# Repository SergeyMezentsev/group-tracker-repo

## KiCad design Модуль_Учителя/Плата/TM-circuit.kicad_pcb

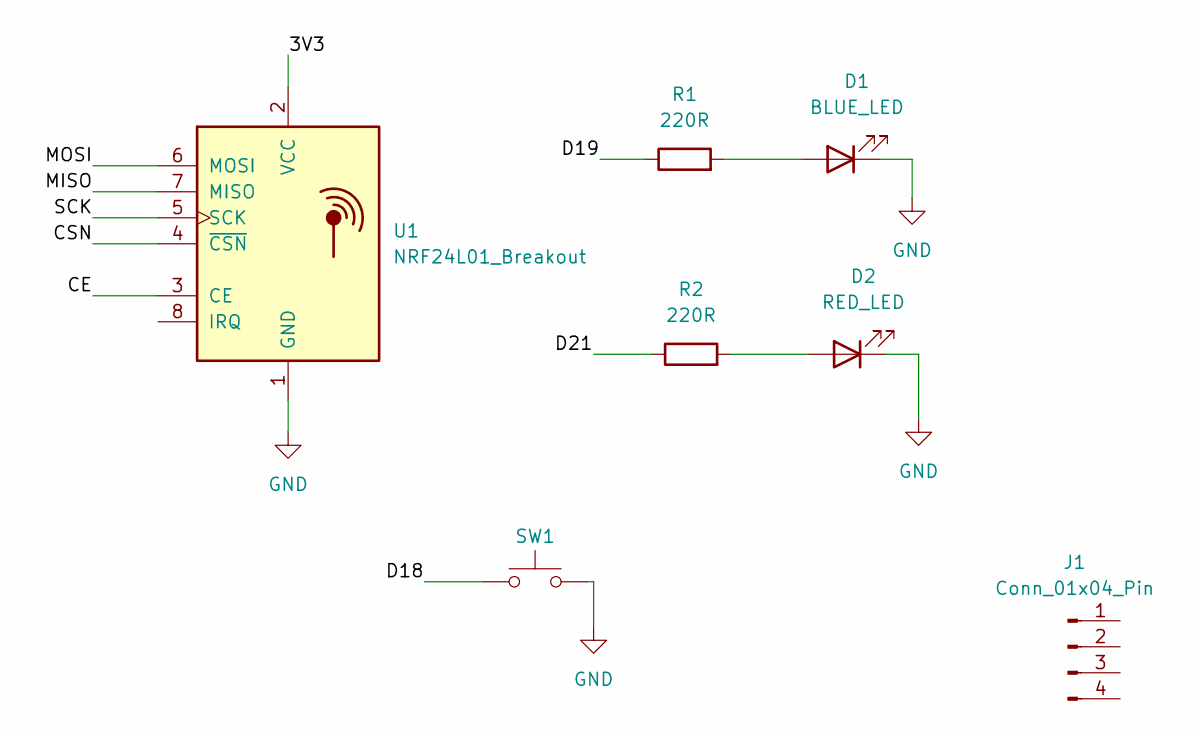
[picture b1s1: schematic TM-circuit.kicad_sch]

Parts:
D1: BLUE_LED; LED_D5.0mm
D2: RED_LED; LED_D5.0mm
J1: Conn_01x04_Pin; PinHeader_1x04_P2.54mm_Vertical
R1, R2: 220R; R_Axial_DIN0207_L6.3mm_D2.5mm_P7.62mm_Horizontal
SW1: SW_Push; SW_PUSH_6mm
U1: NRF24L01_Breakout; nRF24L01_Breakout

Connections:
/3V3: J1.4, U1.2 (VCC)
/CE: U1.3 (CE)
/CSN: U1.4 (~CSN)
/D18: SW1.1
/D19: R1.1
/D21: R2.1
/MISO: U1.7 (MISO)
/MOSI: U1.6 (MOSI)
/SCK: U1.5 (SCK)
GND: D1.1 (K), D2.1 (K), J1.1, SW1.2, U1.1 (GND)
IRQ: U1.8 (IRQ)
unnamed: D1.2 (A), R1.2
unnamed: D2.2 (A), R2.2
RX2: J1.2
TX2: J1.3

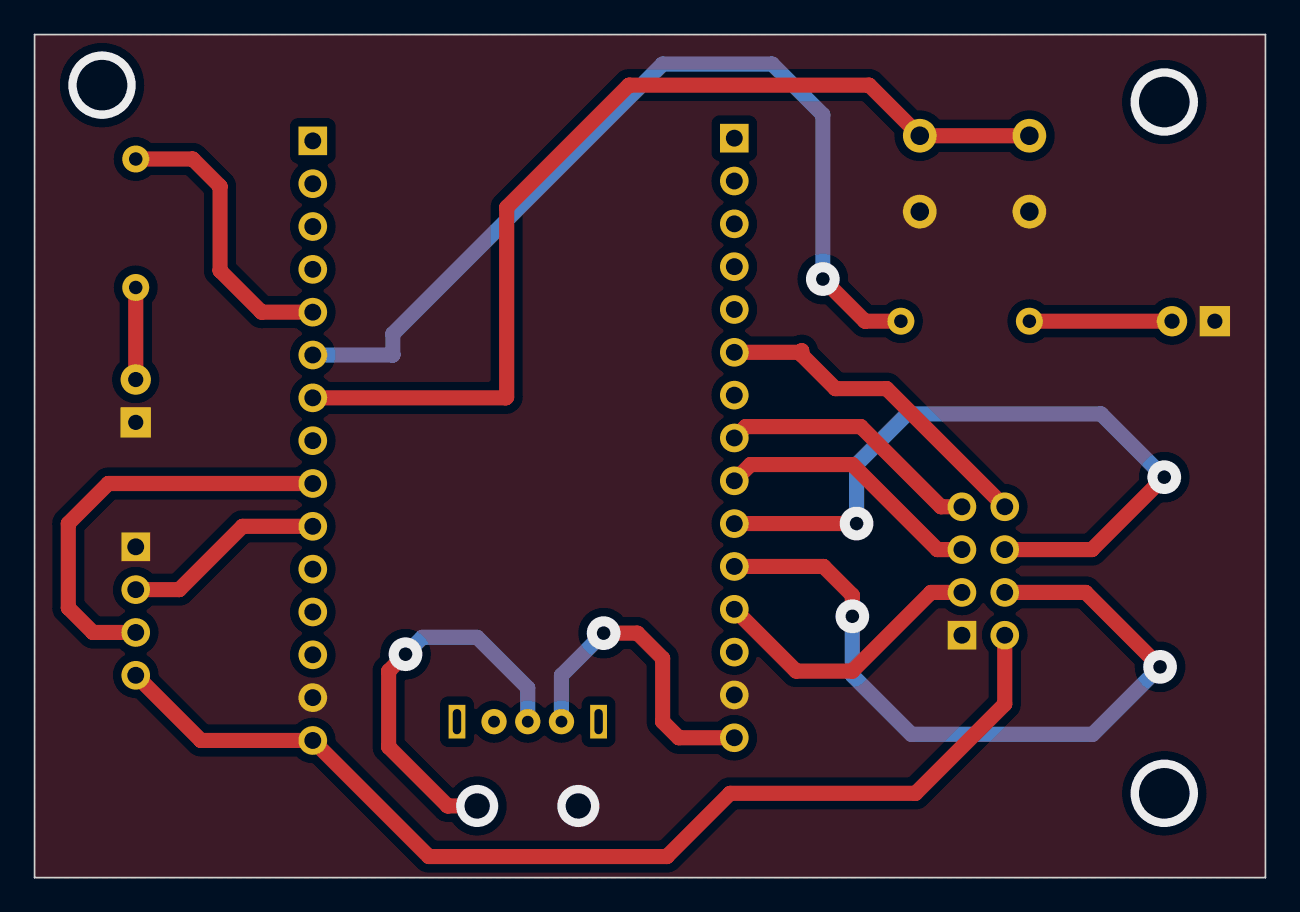
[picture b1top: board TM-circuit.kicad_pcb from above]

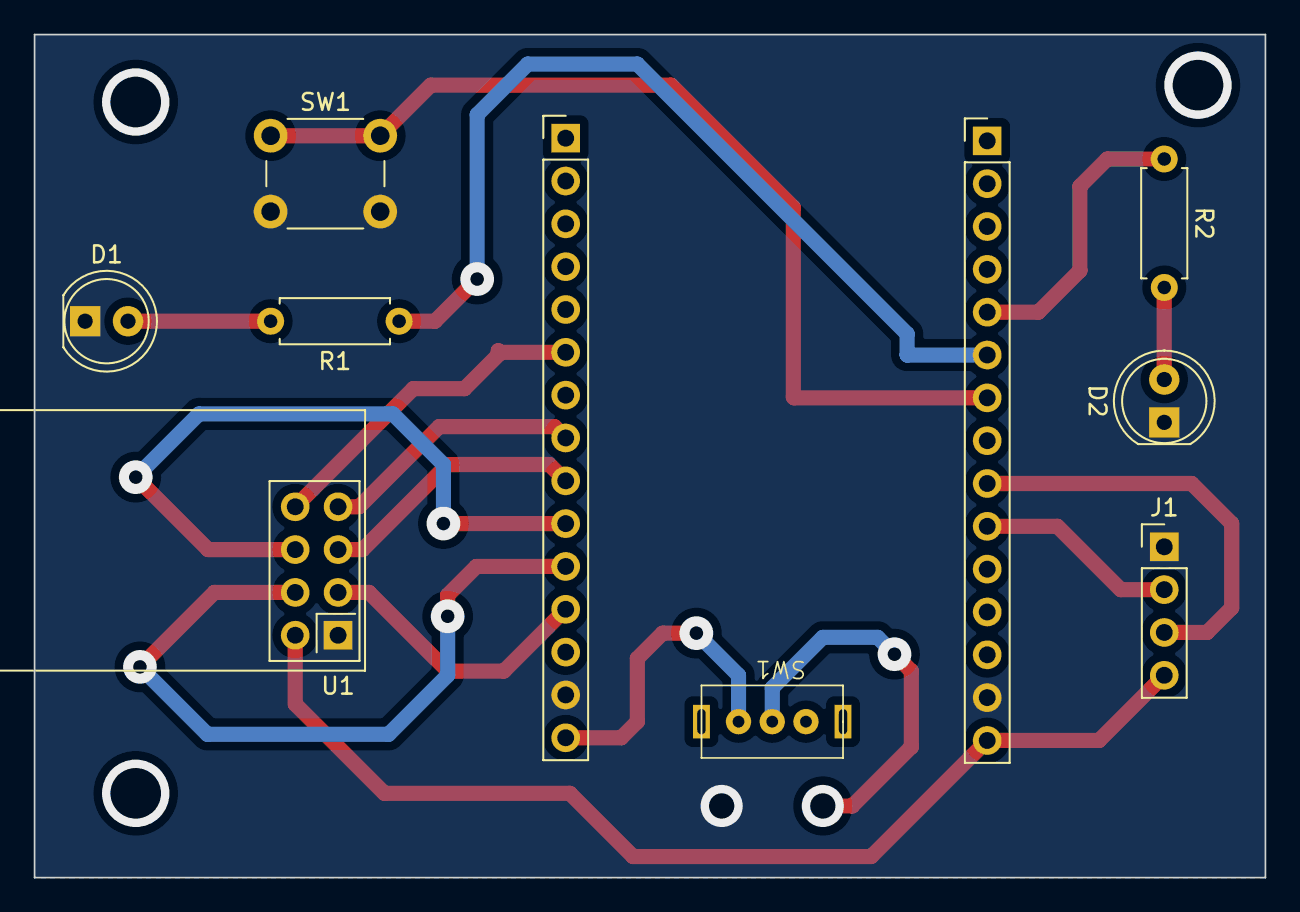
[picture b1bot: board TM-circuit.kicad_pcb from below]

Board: 2 copper layers, 73.0 x 50.0 mm, 8 parts (8 on the bottom side), 4 nets.

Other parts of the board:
SW1#2: SW_SPDT; supply_switch

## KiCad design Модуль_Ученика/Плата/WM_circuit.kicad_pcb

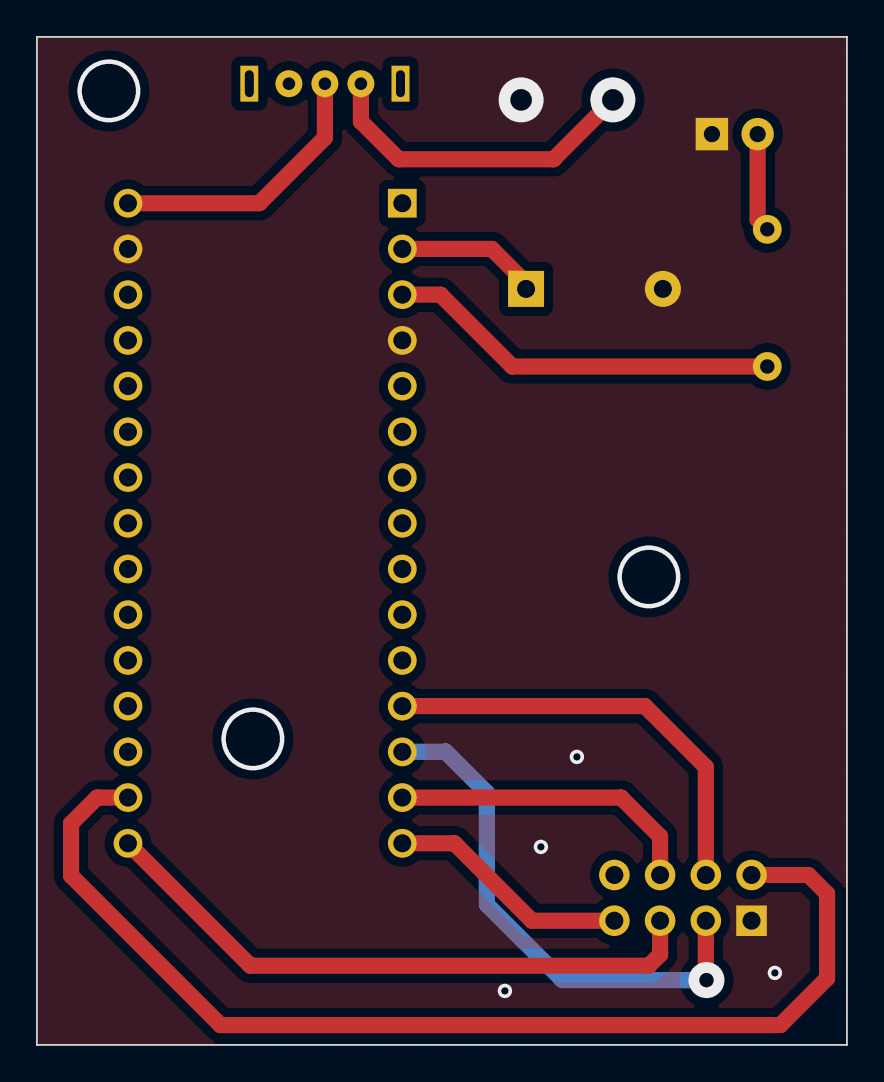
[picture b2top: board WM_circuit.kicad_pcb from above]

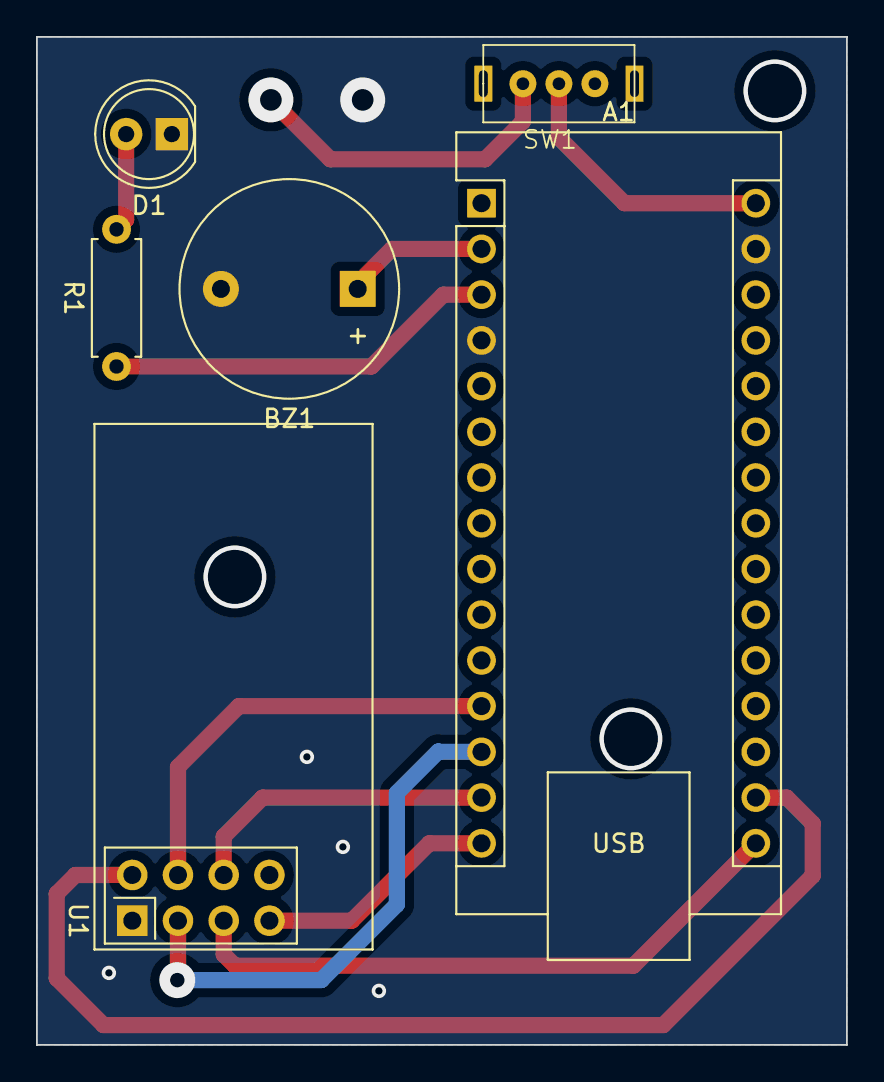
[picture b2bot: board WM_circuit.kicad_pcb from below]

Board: 2 copper layers, 45.0 x 56.0 mm, 6 parts (6 on the bottom side), 11 nets.

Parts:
A1: Arduino_Nano_v3.x; Arduino_Nano
BZ1: Buzzer; Buzzer_12x9.5RM7.6
D1: LED; LED_D5.0mm
R1: R; R_Axial_DIN0207_L6.3mm_D2.5mm_P7.62mm_Horizontal
SW1: SW_SPDT; supply_switch
U1: NRF24L01_Breakout; nRF24L01_Breakout

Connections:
+9V: SW1.1 (A), SW1.5
/3V3: A1.17 (3V3), U1.2 (VCC)
/CE: A1.13 (D10), U1.3 (CE)
/CSN: A1.12 (D9), U1.4 (~CSN)
/MISO: A1.15 (D12), U1.7 (MISO)
/MOSI: A1.14 (D11), U1.6 (MOSI)
/SCK: A1.16 (D13), U1.5 (SCK)
GND: A1.4 (GND), A1.29 (GND), BZ1.2 (+), D1.1 (K), U1.1 (GND)
unnamed: A1.2 (D0/RX), BZ1.1 (-)
unnamed: A1.3 (~RESET), R1.1
unnamed: D1.2 (A), R1.2

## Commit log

2023-10-09 adding all info
2023-10-09 change the presentation
